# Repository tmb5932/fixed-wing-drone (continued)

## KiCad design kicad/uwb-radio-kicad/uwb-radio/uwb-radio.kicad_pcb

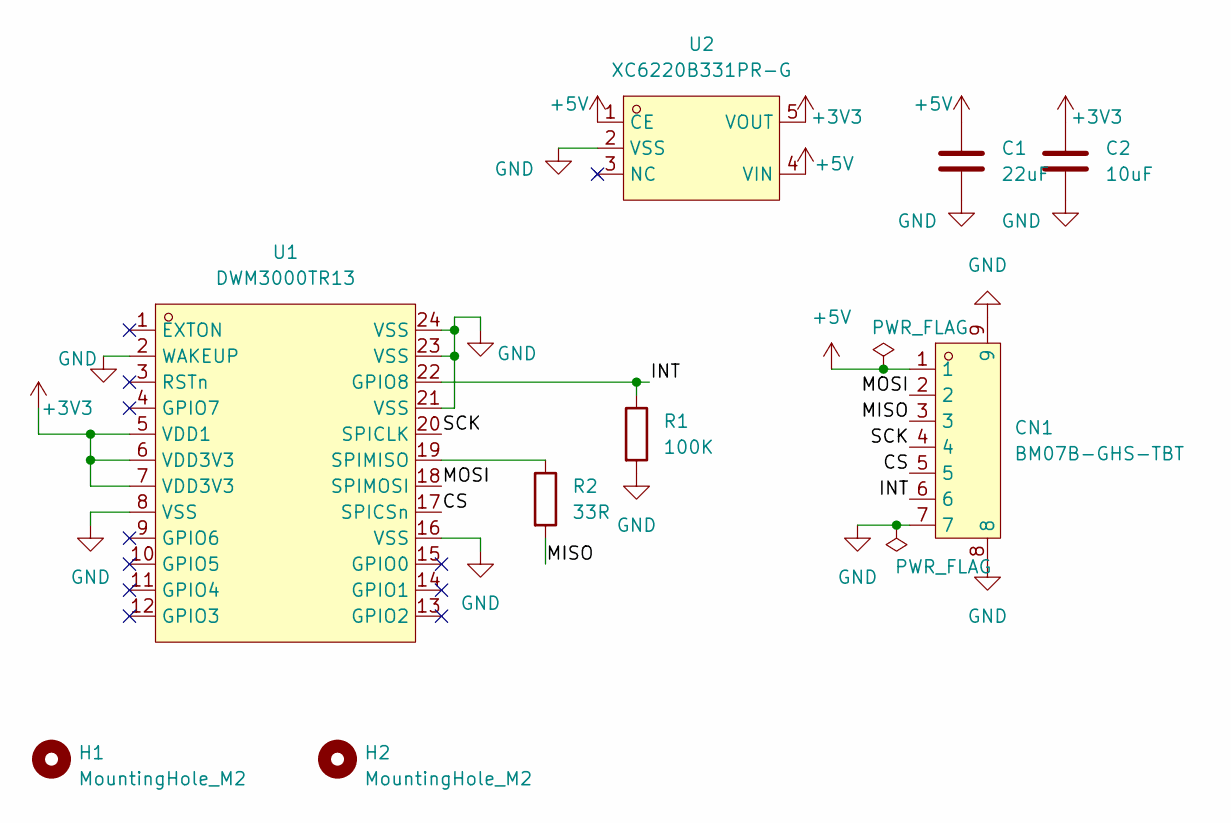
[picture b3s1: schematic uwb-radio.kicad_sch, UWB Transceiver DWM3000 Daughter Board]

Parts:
C1: 22uF; C_0805_2012Metric_Pad1.18x1.45mm_HandSolder; MPN CL21A226MAQNNNE; LCSC Part C45783
C2: 10uF; C_0805_2012Metric_Pad1.18x1.45mm_HandSolder; MPN CL21A106KAYNNNE; LCSC Part C15850
CN1: BM07B-GHS-TBT; CONN-SMD_7P-P1.25_BM07B-GHS-TBT-LF-SN-N; MPN BM07B-GHS-TBT(LF)(SN)(N); LCSC Part C378970
H1, H2: MountingHole_M2; MountingHole_2.2mm_M2
R1: 100K; R_0402_1005Metric_Pad0.72x0.64mm_HandSolder; MPN RC0402FR-07100KL; DigiKey PN 311-100KLRCT-ND
R2: 33R; R_0603_1608Metric_Pad0.98x0.95mm_HandSolder
U1: DWM3000TR13; WIRELM-SMD_DWM3000TR13; MPN DWM3000TR13; LCSC Part C5299931
U2: XC6220B331PR-G; SOT-89-5_L4.5-W2.5-P1.50-LS4.4-BR; MPN XC6220B331PR-G; LCSC Part C3013658

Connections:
+3V3: C2.1, U1.5 (VDD1), U1.6 (VDD3V3), U1.7 (VDD3V3), U2.5 (VOUT)
+5V: C1.1, CN1.1, U2.1 (CE), U2.4 (VIN)
/CS: CN1.5, U1.17 (SPICSn)
/INT: CN1.6, R1.1, U1.22 (GPIO8)
/MISO: CN1.3, R2.2
/MOSI: CN1.2, U1.18 (SPIMOSI)
/SCK: CN1.4, U1.20 (SPICLK)
GND: C1.2, C2.2, CN1.7, CN1.8, CN1.9, R1.2, U1.2 (WAKEUP), U1.8 (VSS), U1.16 (VSS), U1.21 (VSS), U1.23 (VSS), U1.24 (VSS), U2.2 (VSS)
unnamed: R2.1, U1.19 (SPIMISO)

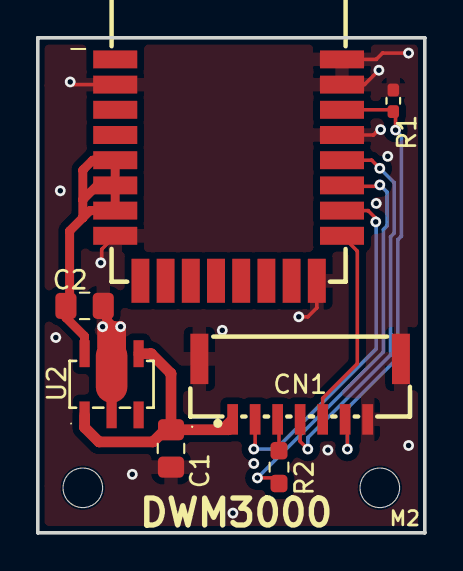
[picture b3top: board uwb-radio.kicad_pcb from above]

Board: 2 copper layers, 21.5 x 27.5 mm, 9 parts (0 on the bottom side), 9 nets.

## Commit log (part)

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2026-03-20 initial commit with basic working implementation of servos
2026-03-20 moved mcpwm output control code to its own .c / .h files
2026-03-20 created .c / .h for mcpwm capture input logic
2026-03-20 main & cmake updated for new files
2026-03-21 esp32s3 cannot have custom resolutions on capture, so added post capture math to solve for it
2026-03-21 made all creation no longer auto choose index, as it was over complicating for no reason
2026-03-21 Current setup can switch between manual pass-through and ignore input mode.
2026-03-24 added time to avoid using old pulse widths
2026-03-26 created empty file for imu processing
2026-03-26 using esp defined constants now instead of hard coding
2026-03-26 same as last
2026-03-26 realized sdkconfig might be important
2026-05-15 added ds store...
2026-05-15 added arduino's MadgwickAHRS filter code
2026-05-15 wrapper to support madgwick usage in c
2026-05-15 added both to the cmake
2026-05-15 created idf component but then never used it so its here but empty now
2026-05-15 IMU works! roll and pitch are all i need for now!
2026-05-15 added mutex for imu data
2026-05-15 added mutex stuff to .h & cleaned up main.c
2026-05-15 added pid functions (NOT TUNED/SETUP)
2026-05-15 added led for debugging
2026-05-15 removed led stuff. issue was overlappng GPIO
2026-05-15 removed extra led stuff
2026-05-16 changed pins imu uses
2026-05-23 cleaned up comments
2026-05-23 moved .h files to includes folder
2026-05-23 copied over gps driver from my other repo
2026-05-23 moved shared imu_data to imu.c/.h instead of main
2026-05-23 updated how PID logic is controlled, and cleaned up some code
2026-05-25 moving peripheral initialization calls to inside respective tasks
